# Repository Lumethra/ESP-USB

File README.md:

# ESP-USB

## What is this? 

This is a "wireless" USB-cable for USB devices. It can "wirelessify" (almost) any USB device with only 2 ESP32-S3's. It can be powered by 5V or even by a 3.7V LiPo battery on the senders side (the side with the USB device). I also features a minimal latency of 2ms, or sometimes even less!!!

### Features: 
- send HID-Protocols wirelessly
- pass the HID-Protocol to the PC with tinyusb
- 1 USB-C
- 1 Status-LED
- 3.7V to 5V booster
- 5V to 3.3V converter
- LiPo battery charger and protector
- 2 buttons, boot and reset
- custom USB-C-CC-Pins-handling

---

## Why? 

I got a new keyboard and wanted it to be wireless. It wasnt possible to do this from the firmware side, because it uses a rpi pico 2 as MCU and upgrading it to a rpi pico 2W wont do much because ZMK doesnt like the bluetooth feature of it. So I thought if it was possible to send the HID-reports, which the keyboard is sending constantly over 2.4Ghz, so the wifi bandwith. After some research I found out that the ESP32-S3 features USB-OTG, so it can read these reports and send them over ESP-Now, a custom "wifi" specifically for ESPs. This will reduce latency by alot. 

--- 

## How?

There are 2 ways of making this project. 1 DIY-version and 1 PCB-version. If you have 2 ESP32-S3-Wroom-1 Devboards, feel free to take the DIY road. 

### DIY:

To replicate this project with 2 ESP32-S3-Devkit-C's you simply just need to download the 2 firmwares, the senders and the recievers. The [ESP-IDF-extension](https://docs.espressif.com/projects/vscode-esp-idf-extension/en/latest/index.html) for [VS-Code](https://code.visualstudio.com/) is also required to flash the firmware. Flashing the firmware is also really easy. After sucessfully installing the ESP-IDF-extension, open the firmware of the reciever by going to the top left and selecting file > open folder > and open the folder containing the reciever firmware. Then go to the bottom bar and select UART for the flash method, its the button with the small little star. We also need to specifiy the COM-port of the ESP. Finding that out is OS-specific, but there are also alot of tutorials for this. For the IDF-Target, select ESP32-S3, since thats out device. Now we are almost finished. The last step we need to take is building and flashing the firmware. We can archieve this by clicking the fire icon a bit more on the right. This will build and flash the firmware. Now repeat this exact precess with the sender and you will have a working ESP-USB-cable. 

<details>
  <summary>
    <h4>TL;DR</h4>
  </summary> 

  - download VS-Code and the ESP-IDF extension
  - download the firmware
  - open the folder with the firmware
  - select UART for flash method
  - select the COM-Port
  - select ESP32-S3 as device
  - press the small fire to build and flash
  - repeat for 2nd device
</details>

### PCB: 

When deciding to use my custom PCB, which is smaller, we need to first order it. JLCPCB for example is a pretty good option. After having it in person, we need to connect it to our PC and hold the boot button while pressing the reset button once. After pressing the reset button we can release the boot button for now. This will set the ESP into download mode and we can flash it exactly like a ESP32-S3-Devkit-C. How this works is explained in the DIY-section above. After flashing both the reciever and the sender we need to decide on a way to power our sender (the one on the USB device side), because it needs to power our USB-device. There are 2 ways, one is connecting a LiPo battery and the other is using 2 of the 4 test pads. The LiPo battery is straight forward, but for the test pads you need 2 cables and a usb breakout board to power the pcb with 5V and GND. After all these steps you can have fun with your wireless usb cable then. 

<details>
  <summary>
    <h4>TL;DR</h4>
  </summary> 

  - order PCB
  - hold boot button
  - press reset button while boot button is hold down
  - release boot button
  - flash firmware (look [here](https://github.com/Lumethra/ESP-USB/blob/main/README.md#diy))
  
</details>

---

### Version differences

### V1:

  - small and compact
  - expensive for PCBA
  - components are exact the same as V2

### V2:

  - slightly bigger than V1
  - waaay cheaper
  - components are exact the same as V1

### V3:

  - biggest
  - adding USB-A-female connector
  - cheaper LED to save cost

---

## Renders

| PCB V1 |
| --- |
|  |
|  |

| PCB V2 |
| --- |
|  |
|  |

| PCB V3 |
| --- |
|  |
|  |

---

## PCB + Schematics

| PCB V1 |
| --- |
|  |

| PCB V2 |
| --- |
|  |

| PCB V3 |
| --- |
|  |

| Schematics V1/V2 |
| --- |
|  |

| Schematics V3 |
| --- |
|  |

---

<details>
  <summary>
    <h2>Zine</h2> 
  </summary>

| Zine |
| --- |
|  |

---
</details>

## BOM DIY

| Part | Purpose | Cost | Quantity | Total Cost | LCSC/JLCPCB Number | Link | 
| --- | --- | --- | --- | --- | --- | --- |
| ESP-32-Devkit-C | run things | $15.07 | 2 | $30.14 | ~ | [AMAZON](https://www.amazon.de/diymore-DevKitC-Development-Bluetooth-Soldered-1-piece/dp/B0CYZVQR27/?language=en_GB&currency=USD) | 
| Powered USB Hub | the usb port doesnt provide 5V and GND | ~ (already owned) | 1 | ~ (already owned) | ~ | 
| USB Device | the device u wanna make wireless | ~ (already owned) | 1 | ~ (already owned) | ~ | 
| Computer | ur computer that u wanna connect the usb device to | ~ (already owned) | 1 | ~ (already owned) | ~ | 

## BOM PCB 

| Part | Purpose | Cost | Quantity | Total Cost | LCSC/JLCPCB Number | Link | 
| --- | --- | --- | --- | --- | --- | --- |
| PCB | connecting every component | ~$2.00 | 1 (5) | ~$2.00 | ~ | [JLCPCB](https://jlcpcb.com/) |
| Capacitors 100nF | clean up power | $0.0084 | 2 | $0.0168 | C14663 | [JLCPCB](https://jlcpcb.com/partdetail/C14663) |
| Capacitors 4.7uF | cleaning power | $0.0140 | 2 | $0.0280 | C19666 | [JLCPCB](https://jlcpcb.com/partdetail/C19666) |
| Capacitor 22uF | make power clean | $0.0149 | 1 | $0.0149 | C59461 | [JLCPCB](https://jlcpcb.com/partdetail/C59461) |
| Capacitors 10uF | power gets clean | $0.0139 | 2 | $0.0278 | C19702 | [JLCPCB](https://jlcpcb.com/partdetail/C19702) |
| S2B-PH-SM4-TB | battery connector | $0.2040 | 1 | $0.2040 | C295747 | [JLCPCB](https://jlcpcb.com/partdetail/C295747) |
| SK6812 | LED | $0.0894 | 1 | $0.0894 | C5378720 | [JLCPCB](https://jlcpcb.com/partdetail/C5378720) |
| SS14 Schottky Diodes | good "one way door" | $0.0169 | 2 | $0.0338 | C2480 | [JLCPCB](https://jlcpcb.com/partdetail/C2480) |
| Inductor 4.7uH | energy storage | $0.0324 | 1 | $0.0324 | C395016 | [JLCPCB](https://jlcpcb.com/partdetail/C395016) |
| FS8205A | mosfet | $0.0575 | 1 | $0.0575 | C2830320 | [JLCPCB](https://jlcpcb.com/partdetail/C2830320) |
| Resistors 5.1k | prevent booom | $0.0016 | 4 | $0.0064 | C23186 | [JLCPCB](https://jlcpcb.com/partdetail/C23186) |
| Resistors 1k | no booom | $0.0016 | 3 | $0.0048 | C21190 | [JLCPCB](https://jlcpcb.com/partdetail/C21190) |
| Resistor 100k | aww | $0.0018 | 1 | $0.0018 | C25803 | [JLCPCB](https://jlcpcb.com/partdetail/C25803) |
| Resistor 33k | ahh, we want boom | $0.0015 | 1 | $0.0015 | C4216 | [JLCPCB](https://jlcpcb.com/partdetail/C4216) |
| Resistors 56k | no we dont | $0.0016 | 2 | $0.0032 | C23206 | [JLCPCB](https://jlcpcb.com/partdetail/C23206) |
| Resistor 100 | so resistors exist | $0.0019 | 1 | $0.0019 | C22775 | [JLCPCB](https://jlcpcb.com/partdetail/C22775) |
| RST Button | restarts the esp | $0.0206 | 1 | $0.0206 | C318884 | [JLCPCB](https://jlcpcb.com/partdetail/C318884) |
| BOOT Button | lets esp go into download mode | $0.0206 | 1 | $0.0206 | C318884 | [JLCPCB](https://jlcpcb.com/partdetail/C318884) |
| ESP32-S3-WROOM-1 | handeling firmware | $5.3893 | 1 | $5.3893 | C2913202 | [JLCPCB](https://jlcpcb.com/partdetail/C2913202) |
| 74LVC1G3157DW-7 | switch for cc pins | $0.0685 | 2 | $0.1370 | C176651 | [JLCPCB](https://jlcpcb.com/partdetail/C176651) |
| DW01A | battery protector | $0.0428 | 1 | $0.0428 | C351410 | [JLCPCB](https://jlcpcb.com/partdetail/C351410) |
| MCP73831T-2ACI/OT | battery charger | $0.8122 | 1 | $0.8122 | C424093 | [JLCPCB](https://jlcpcb.com/partdetail/C424093) |
| MT3608 | 3.7v to 5v | $0.0786 | 1 | $0.0786 | C84817 | [JLCPCB](https://jlcpcb.com/partdetail/C84817) |
| AMS1117-3.3 | 5v to 3.3v | $0.2036 | 1 | $0.2036 | C6186 | [JLCPCB](https://jlcpcb.com/partdetail/C6186) |
| USB-C Connector | connects the dongle to pcb or whatever | $0.0741 | 1 | $0.0741 | C2765186 | [JLCPCB](https://jlcpcb.com/partdetail/C2765186) |
| **Total** |  | **~$9.48**  |  | **~$9.48** <br> _+ PCBA cost_  |  |  |

---

## Contribute

Want to make it better? Found some bugs? Feel free to open a PR (pull request) and lets make the project better. ^_^
> the libraries are all imported with [easyeda2kicad](https://github.com/uPesy/easyeda2kicad.py)

--- 

## Thank you

huge thank you too all these persons helping me making this project possible, thank you helping me sanity check, thank you for all these support. 
> Thank you, <3 u all ^_^

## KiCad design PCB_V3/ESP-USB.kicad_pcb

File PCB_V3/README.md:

# V3

Changes: 

    - adding USB-A
    - changing to a cheaper RGB-LED
        - meaning you can try solder the wroom yourself and get economics PCBA

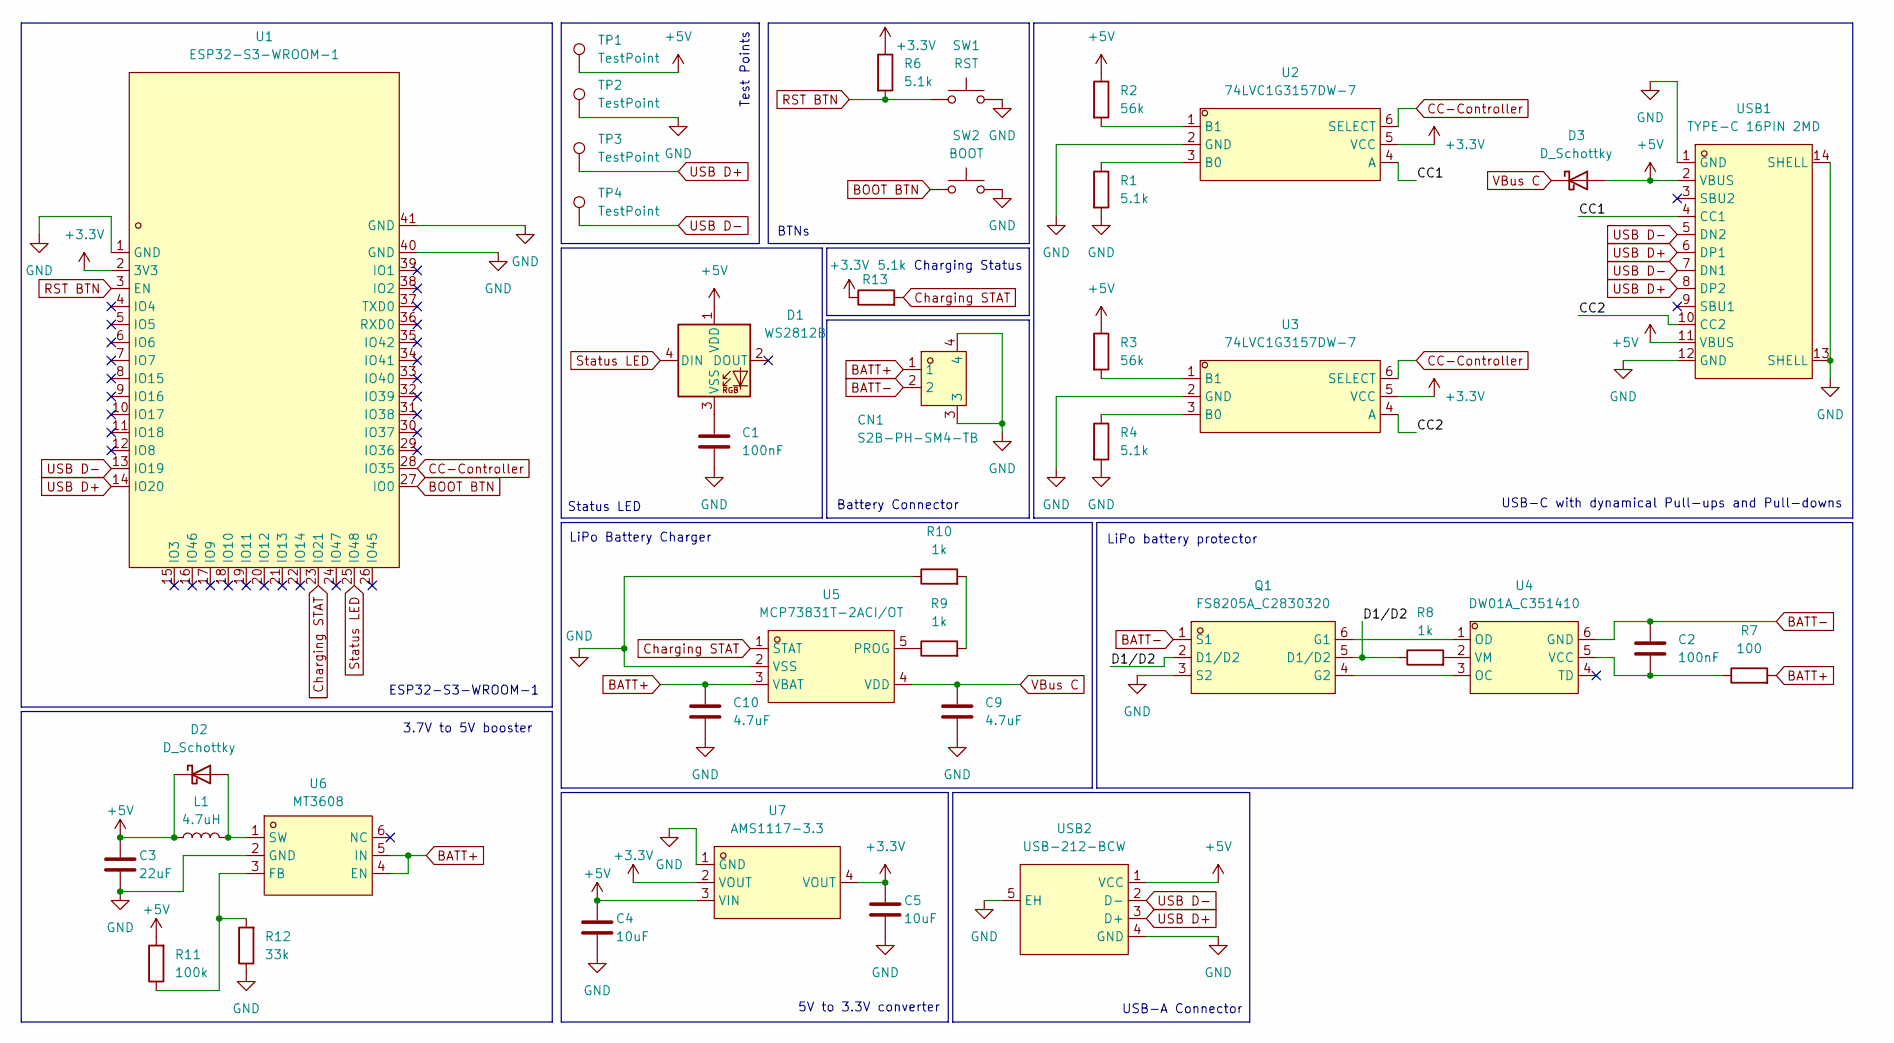
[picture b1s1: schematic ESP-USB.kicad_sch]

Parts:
C1, C2: 100nF; C_0603_1608Metric; LCSC Part C14663
C3: 22uF; C_0603_1608Metric; LCSC Part C59461
C4, C5: 10uF; C_0603_1608Metric; LCSC Part C19702
C9, C10: 4.7uF; C_0603_1608Metric; LCSC Part C19666
CN1: S2B-PH-SM4-TB; CONN-SMD_P2.00_S2B-PH-SM4-TB-LF-SN; MPN S2B-PH-SM4-TB(LF)(SN); LCSC Part C295747
D1: WS2812B; LED_WS2812B_PLCC4_5.0x5.0mm_P3.2mm; LCSC Part C42417498
D2, D3: D_Schottky; D_SMA; LCSC Part C2480
L1: 4.7uH; L_0805_2012Metric; LCSC Part C395016
Q1: FS8205A_C2830320; SOT-23-6_L2.9-W1.6-P0.95-LS2.8-BR; MPN FS8205A; LCSC Part C2830320
R1, R4, R6, R13: 5.1k; R_0603_1608Metric; LCSC Part C23186
R2, R3: 56k; R_0603_1608Metric; LCSC Part C23206
R7: 100; R_0603_1608Metric; LCSC Part C22775
R8, R9, R10: 1k; R_0603_1608Metric; LCSC Part C21190
R11: 100k; R_0603_1608Metric; LCSC Part C25803
R12: 33k; R_0603_1608Metric; LCSC Part C4216
SW1: RST; SW_Push_1TS009xxxx-xxxx-xxxx_6x6x5mm; LCSC Part C318884
SW2: BOOT; SW_Push_1TS009xxxx-xxxx-xxxx_6x6x5mm; LCSC Part C318884
TP1, TP2, TP3, TP4: TestPoint; TestPoint_Pad_2.0x2.0mm
U1: ESP32-S3-WROOM-1; WIRELM-SMD_ESP32-S3-WROOM-1; MPN ESP32-S3-WROOM-1-N16R8; LCSC Part C2913202
U2, U3: 74LVC1G3157DW-7; SOT-363-6_L2.2-W1.3-P0.65-LS2.1-BL; MPN 74LVC1G3157DW-7; LCSC Part C176651
U4: DW01A_C351410; SOT-23-6_L2.9-W1.6-P0.95-LS2.8-BL; MPN DW01A; LCSC Part C351410
U5: MCP73831T-2ACI/OT; SOT-23-5_L3.0-W1.7-P0.95-LS2.8-BL; MPN MCP73831T-2ACI/OT; LCSC Part C424093
U6: MT3608; SOT-23-6_L2.9-W1.6-P0.95-LS2.8-BL; MPN MT3608; LCSC Part C84817
U7: AMS1117-3.3; SOT-223-3_L6.5-W3.4-P2.30-LS7.0-BR; MPN AMS1117-3.3; LCSC Part C6186
USB1: TYPE-C 16PIN 2MD; USB-C-SMD_TYPE-C-6PIN-2MD-073; MPN TYPE-C 16PIN 2MD(073); LCSC Part C2765186
USB2: USB-212-BCW; USB-A-SMD_USB-212-BCW; MPN USB-212-BCW; LCSC Part C720521

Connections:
+3.3V: C5.1, R6.1, R13.1, U1.2 (3V3), U2.5 (VCC), U3.5 (VCC), U7.2 (VOUT), U7.4 (VOUT)
+5V: C3.1, C4.1, D1.1 (VDD), D2.1 (K), D3.2 (A), L1.1, R2.1, R3.1, R11.2, TP1.1 (1_1), U7.3 (VIN), USB1.2 (VBUS), USB1.11 (VBUS), USB2.1 (VCC)
/CC1: U2.4 (A), USB1.4 (CC1)
/CC2: U3.4 (A), USB1.10 (CC2)
/D1/D2: Q1.2 (D1/D2), Q1.5 (D1/D2), R8.1
BATT+: C10.1, CN1.1, R7.2, U5.3 (VBAT), U6.4 (EN), U6.5 (IN)
BATT-: C2.1, CN1.2, Q1.1 (S1), U4.6 (GND)
BOOT BTN: SW2.1, U1.27 (IO0)
CC-Controller: U1.28 (IO35), U2.6 (SELECT), U3.6 (SELECT)
Charging STAT: R13.2, U1.23 (IO21), U5.1 (STAT)
GND: C1.2, C3.2, C4.2, C5.2, C9.2, C10.2, CN1.3, CN1.4, Q1.3 (S2), R1.2, R4.2, R10.1, R12.1, SW1.2, SW2.2, TP2.1 (1_1), U1.1 (GND), U1.40 (GND), U1.41 (GND), U2.2 (GND), U3.2 (GND), U5.2 (VSS), U6.2 (GND), U7.1 (GND), USB1.1 (GND), USB1.12 (GND), USB1.13 (SHELL), USB1.14 (SHELL), USB2.4 (GND), USB2.5 (EH)
unnamed: C1.1, D1.3 (VSS)
unnamed: D2.2 (A), L1.2, U6.1 (SW)
unnamed: Q1.6 (G1), U4.1 (OD)
unnamed: Q1.4 (G2), U4.3 (OC)
unnamed: R9.2, R10.2
unnamed: R1.1, U2.3 (B0)
unnamed: R2.2, U2.1 (B1)
unnamed: R4.1, U3.3 (B0)
unnamed: R3.2, U3.1 (B1)
unnamed: C2.2, R7.1, U4.5 (VCC)
unnamed: R8.2, U4.2 (VM)
unnamed: R9.1, U5.5 (PROG)
unnamed: R11.1, R12.2, U6.3 (FB)
RST BTN: R6.2, SW1.1, U1.3 (EN)
Status LED: D1.4 (DIN), U1.25 (IO48)
USB D+: TP3.1 (1_1), U1.14 (IO20), USB1.6 (DP1), USB1.8 (DP2), USB2.3 (D+)
USB D-: TP4.1 (1_1), U1.13 (IO19), USB1.5 (DN2), USB1.7 (DN1), USB2.2 (D-)
VBus C: C9.1, D3.1 (K), U5.4 (VDD)

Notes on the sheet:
5V to 3.3V converter
Test Points
USB-C with dynamical Pull-ups and Pull-downs
Charging Status
LiPo Battery Charger
BTNs
LiPo battery protector
ESP32-S3-WROOM-1
USB-A Connector
3.7V to 5V booster
Status LED
Battery Connector

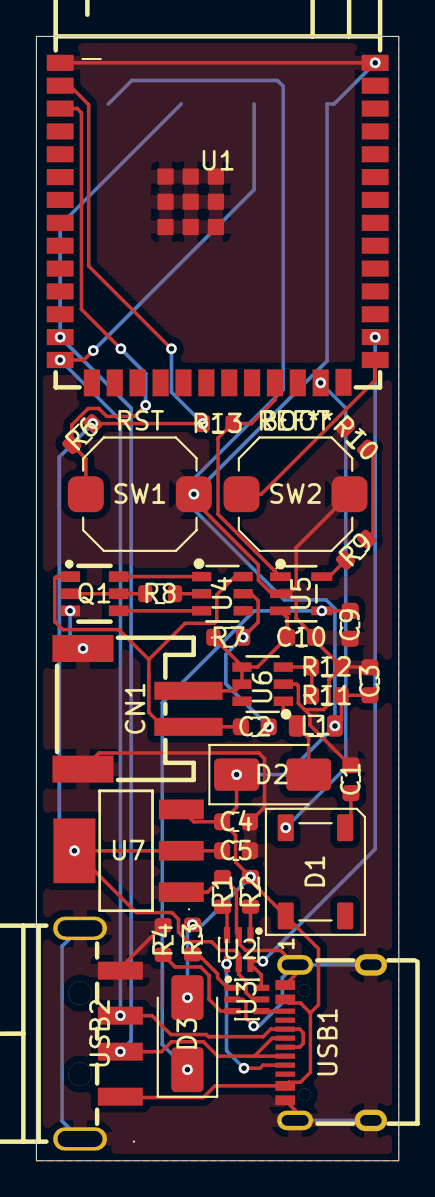
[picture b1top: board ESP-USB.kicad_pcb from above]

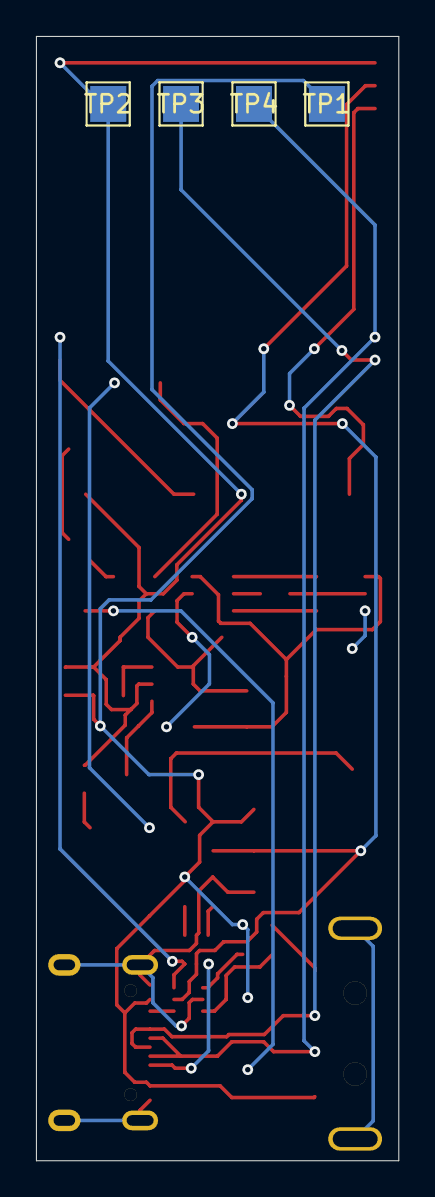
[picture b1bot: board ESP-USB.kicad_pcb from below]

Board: 2 copper layers, 20.1 x 62.5 mm, 40 parts (4 on the bottom side), 29 nets.

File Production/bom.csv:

Name,Designator,Footprint,Quantity,Value,Price,LCSC Part #,Purchase Link
Capacitors 100nF,"C1, C2",0603,2,100nF,$0.0032,C14663,https://jlcpcb.com/partdetail/C14663
Capacitors 4.7uF,"C9, C10",0603,2,4.7uF,$0.0110,C19666,https://jlcpcb.com/partdetail/C19666
Capacitor 22uF,C3,0603,1,22uF,$0.0100,C59461,https://jlcpcb.com/partdetail/C59461
Capacitors 10uF,"C4, C5",0603,2,10uF,$0.0100,C19702,https://jlcpcb.com/partdetail/C19702
S2B-PH-SM4-TB,CN1,CONN-SMD_P2.00_S2B-PH-SM4-TB-LF-SN,1,S2B-PH-SM4-TB,$0.2014,C295747,https://jlcpcb.com/partdetail/C295747
SK6812,D1,LED_SK6812_PLCC4_5.0x5.0mm_P3.2mm,1,SK6812,$0.1000,C5378720,https://jlcpcb.com/partdetail/C5378720
SS14 Schottky Diodes,"D2, D3",D_SMA,2,D_Schottky,$0.0200,C2480,https://jlcpcb.com/partdetail/C2480
Inductor 4.7uH,L1,0805,1,4.7uH,$0.0500,C395016,https://jlcpcb.com/partdetail/C395016
FS8205A,Q1,SOT-23-6_L2.9-W1.6-P0.95-LS2.8-BR,1,FS8205A_C2830320,$0.0470,C2830320,https://jlcpcb.com/partdetail/C2830320
Resistors 5.1k,"R1, R4, R6, R13",0603,4,5.1k,$0.0016,C23186,https://jlcpcb.com/partdetail/C23186
Resistors 1k,"R8, R9, R10",0603,3,1k,$0.0016,C21190,https://jlcpcb.com/partdetail/C21190
Resistor 100k,R11,0603,1,100k,$0.0016,C25803,https://jlcpcb.com/partdetail/C25803
Resistor 33k,R12,0603,1,33k,$0.0016,C4216,https://jlcpcb.com/partdetail/C4216
Resistors 56k,"R2, R3",0603,2,56k,$0.0016,C23206,https://jlcpcb.com/partdetail/C23206
Resistor 100,R7,0603,1,100,$0.0016,C22775,https://jlcpcb.com/partdetail/C22775
RST Button,SW1,SW_Push_1TS009xxxx-xxxx-xxxx_6x6x5mm,1,RST,$0.0500,C318884,https://jlcpcb.com/partdetail/C318884
BOOT Button,SW2,SW_Push_1TS009xxxx-xxxx-xxxx_6x6x5mm,1,BOOT,$0.0500,C318884,https://jlcpcb.com/partdetail/C318884
ESP32-S3-WROOM-1,U1,WIRELM-SMD_ESP32-S3-WROOM-1,1,ESP32-S3-WROOM-1,$4.0000,C2913202,https://jlcpcb.com/partdetail/C2913202
74LVC1G3157DW-7,"U2, U3",SOT-363-6_L2.2-W1.3-P0.65-LS2.1-BL,2,74LVC1G3157DW-7,$0.0500,C176651,https://jlcpcb.com/partdetail/C176651
DW01A,U4,SOT-23-6_L2.9-W1.6-P0.95-LS2.8-BL,1,DW01A_C351410,$0.0426,C351410,https://jlcpcb.com/partdetail/C351410
MCP73831T-2ACI/OT,U5,SOT-23-5_L3.0-W1.7-P0.95-LS2.8-BL,1,MCP73831T-2ACI/OT,$0.7585,C424093,https://jlcpcb.com/partdetail/C424093
MT3608,U6,SOT-23-6_L2.9-W1.6-P0.95-LS2.8-BL,1,MT3608,$0.0667,C84817,https://jlcpcb.com/partdetail/C84817
AMS1117-3.3,U7,SOT-223-3_L6.5-W3.4-P2.30-LS7.0-BR,1,AMS1117-3.3,$0.1120,C6186,https://jlcpcb.com/partdetail/C6186
USB-C Connector,USB1,USB-C-SMD_TYPE-C-6PIN-2MD-073,1,TYPE-C 16PIN 2MD,$0.0740,C2765186,https://jlcpcb.com/partdetail/C2765186

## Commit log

2026-06-04 format bom
2026-06-04 start with readme
2026-06-04 update prices
2026-06-04 minor chnages
2026-06-04 adding some descriptions
2026-06-04 formating links
2026-06-04 adding descriptions
2026-06-04 renaming 1st bom
2026-06-04 making V2
2026-06-04 new bom for v2
2026-06-04 renaming v1 and v2
2026-06-04 add note
2026-06-05 adding renders
2026-06-05 adding one image or two
2026-06-05 adding more images
2026-06-05 writing readme
2026-06-05 adding TL:DR
2026-06-05 wrong link
2026-06-05 changed link
2026-06-05 tl:dr to tl;dr
2026-06-05 adding zine
2026-06-08 zine?
2026-06-13 making V3
2026-06-13 adding v3 renders
2026-06-13 adding v3 pcb in better
2026-06-13 adding v3 schematics
2026-06-13 adding V3
2026-06-13 new zine with V3
